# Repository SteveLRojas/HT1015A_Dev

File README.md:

# HT1015A_Dev
Evaluation board for the HT1015A buck converter.

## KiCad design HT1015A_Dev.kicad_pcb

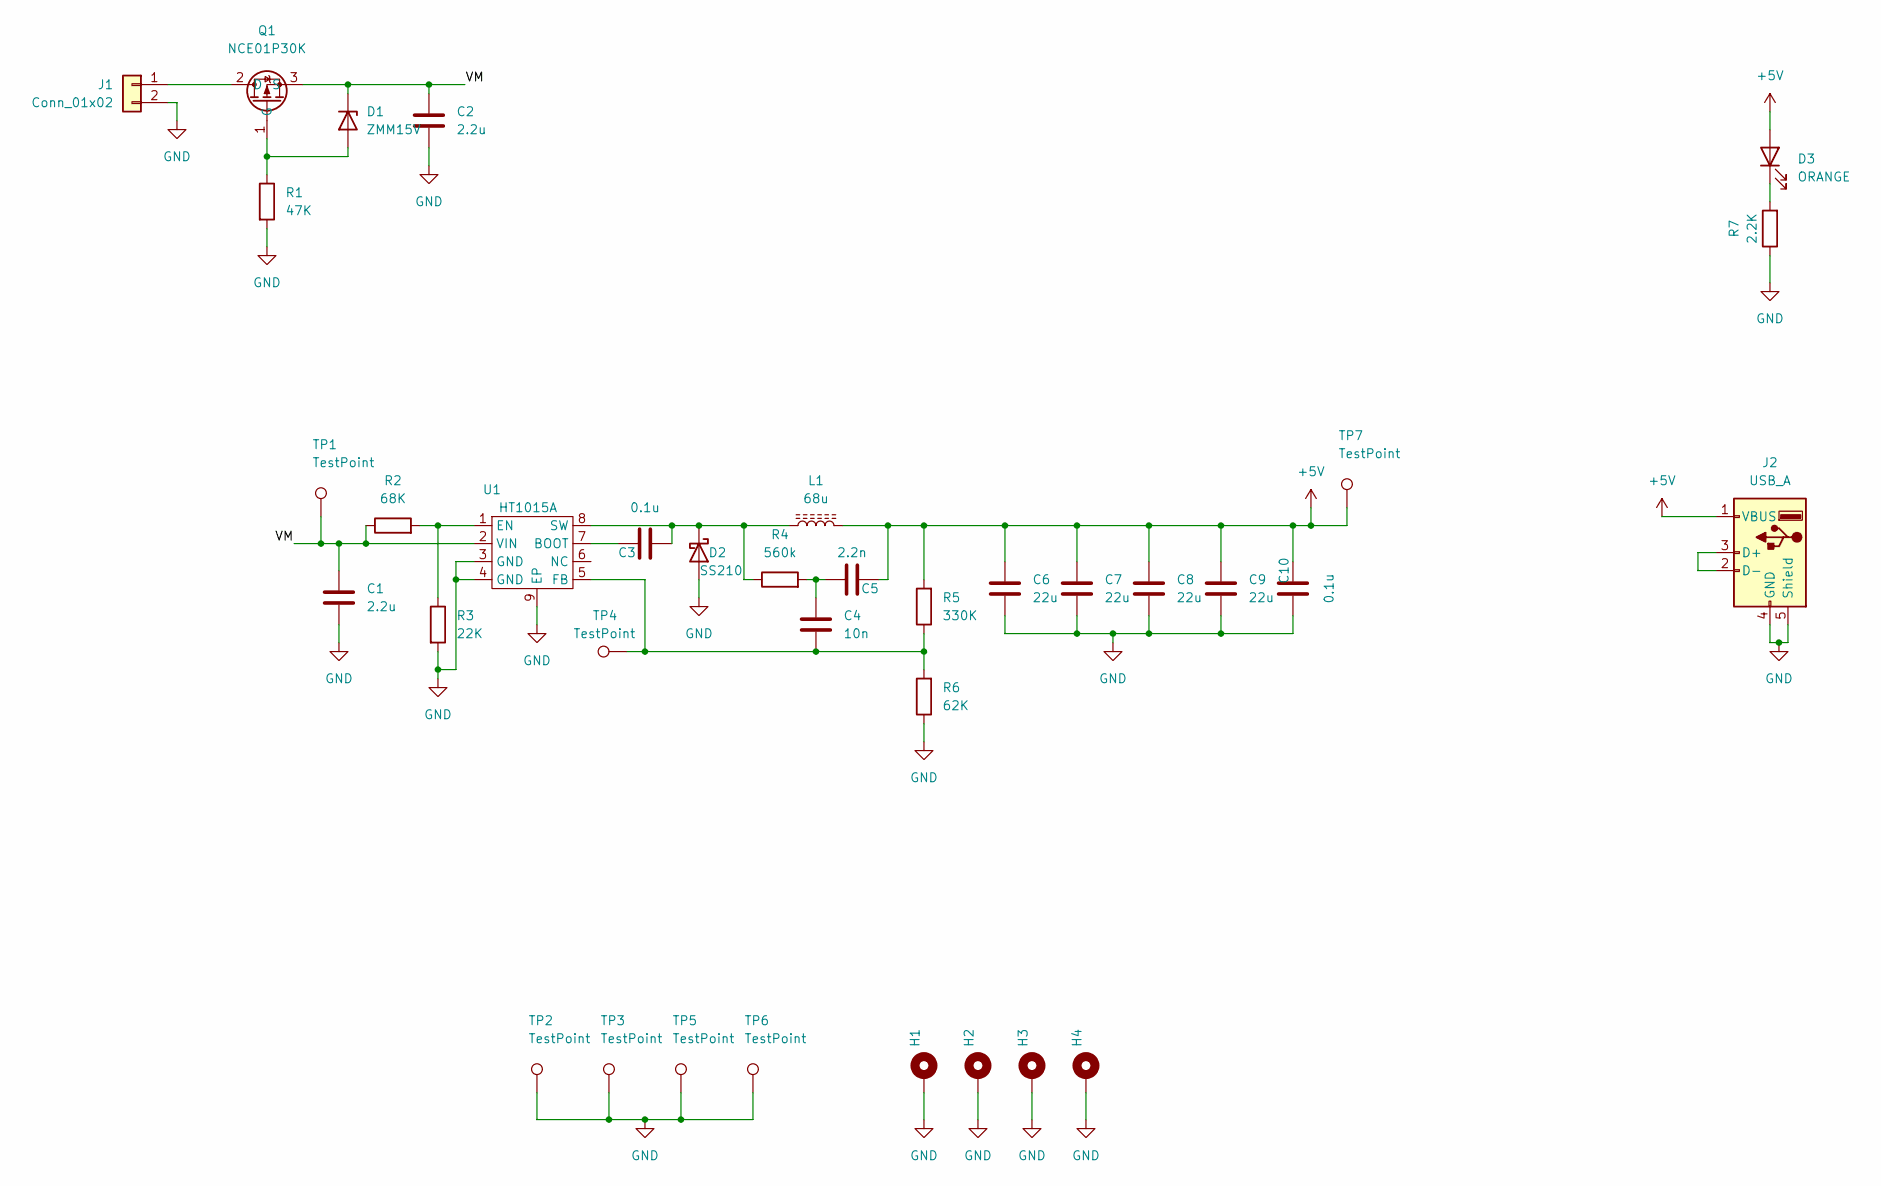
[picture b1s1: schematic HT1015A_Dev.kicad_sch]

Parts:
C1, C2: 2.2u; C_1206_3216Metric
C3, C10: 0.1u; C_0805_2012Metric
C4: 10n; C_0805_2012Metric
C5: 2.2n; C_0805_2012Metric
C6, C7, C8, C9: 22u; C_1206_3216Metric
D1: ZMM15V; D_MiniMELF
D2: SS210; D_SMA
D3: ORANGE; LED_0805_2012Metric
H1, H2, H3, H4: MountingHole_Pad; MountingHole_3.2mm_M3_Pad
J1: Conn_01x02; PhoenixContact_MSTBA_2,5_2-G-5,08_1x02_P5.08mm_Horizontal
J2: USB_A; USB_A_CONNFLY_DS1095-WNR0
L1: 68u; CYA0650-68UH
Q1: NCE01P30K; TO-252-2
R1: 47K; R_0805_2012Metric
R2: 68K; R_0805_2012Metric
R3: 22K; R_0805_2012Metric
R4: 560k; R_0805_2012Metric
R5: 330K; R_0805_2012Metric
R6: 62K; R_0805_2012Metric
R7: 2.2K; R_0805_2012Metric
TP1, TP2, TP3, TP4, TP5, TP6, TP7: TestPoint; TestPoint_Loop_D2.50mm_Drill1.0mm
U1: HT1015A; HSOP-8-1EP_3.9x4.9mm_P1.27mm_EP2.41x3.1mm_ThermalVias

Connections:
+5V: C5.2, C6.2, C7.2, C8.2, C9.2, C10.1, D3.2 (A), J2.1 (VBUS), L1.2, R5.2, TP7.1
/VM: C1.2, C2.2, D1.1 (K), Q1.3 (S), R2.1, TP1.1, U1.2 (VIN)
GND: C1.1, C2.1, C6.1, C7.1, C8.1, C9.1, C10.2, D2.2 (A), H1.1, H2.1, H3.1, H4.1, J1.2, J2.4 (GND), J2.5 (Shield), R1.2, R3.2, R6.1, R7.1, TP2.1, TP3.1, TP5.1, TP6.1, U1.3 (GND), U1.4 (GND), U1.9 (EP)
unnamed: C3.1, U1.7 (BOOT)
unnamed: C3.2, D2.1 (K), L1.1, R4.1, U1.8 (SW)
unnamed: C4.1, R5.1, R6.2, TP4.1, U1.5 (FB)
unnamed: C4.2, C5.1, R4.2
unnamed: D1.2 (A), Q1.1 (G), R1.1
unnamed: D3.1 (K), R7.2
unnamed: J1.1, Q1.2 (D)
unnamed: J2.2 (D-), J2.3 (D+)
unnamed: R2.2, R3.1, U1.1 (EN)

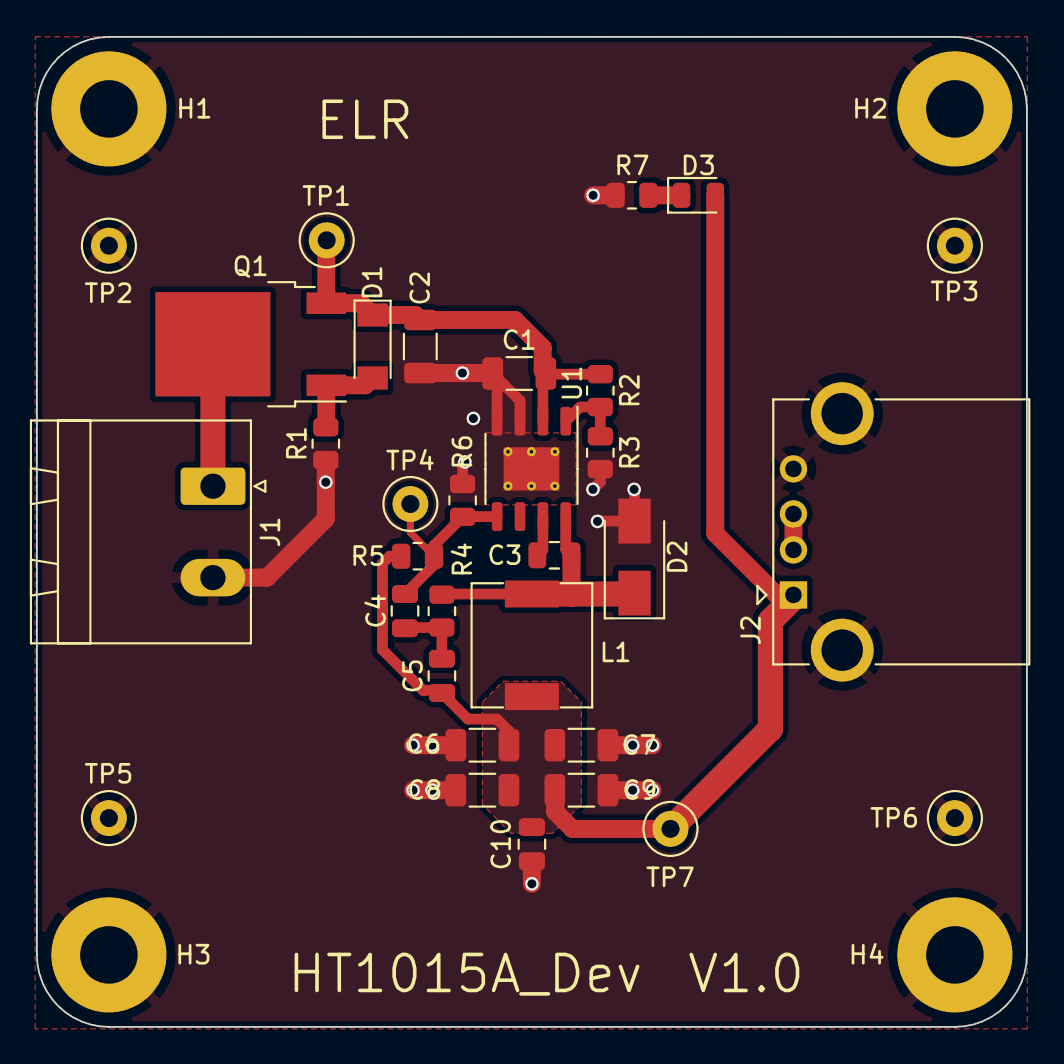
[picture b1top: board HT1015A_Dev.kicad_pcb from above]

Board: 2 copper layers, 55.0 x 55.0 mm, 36 parts (0 on the bottom side), 12 nets.

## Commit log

2025-09-20 Added design files
2025-09-20 Added license
